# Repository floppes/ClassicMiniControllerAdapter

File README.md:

# Nintendo Classic Mini Controller USB Adapter #

This is an adapter for connecting one or two Nintendo Classic Mini controllers via USB to a computer.
It works with the controllers of a Nintendo NES and SNES Classic Mini.

## Motivation ##

I like playing old retro games on a Raspberry Pi running RetroPie on my TV screen. I also have a Nintendo SNES Classic Mini and like the quality and feel of its controllers. So why not connect the controllers to the Raspberry Pi? Well, Nintendo uses their own connectors and protocol which are incompatible with a PC/laptop/Raspberry Pi. But the connectors are available to buy on the Internet and the protocol specification can be found as well. So I created a small piece of hardware around an ATmega32U4 microcontroller to translate the controller's signals to USB.

## Hardware ##

This is basically an Arduino like the Leonardo or [SparkFun Pro Micro](https://www.sparkfun.com/products/12587), running two software I2C buses. It runs at 3.3 Volts and 8 MHz.

### LEDs ###

There are three LEDs on the board. The outer yellow LEDs indicate if a controller on the corresponding port was detected. The ports are hot-pluggable. The green LED in the center indicates that the device has booted and is operational.

### PCB ###

The PCB layout and part list can be found in [schematic](schematic).

You can order the unpopulated board directly from [OSH Park](https://oshpark.com/shared_projects/MKpWshOk).

Most parts can be bought from the usual distributors such as Farnell, DigiKey, Mouser etc. The connectors are a little bit harder to get. You can find them on eBay or AliExpress if you search for **Wiimote connector**. The components cost me about $11.

## Software ##

### Bootloader ###

I recommend flashing the SparkFun Pro Micro 3.3 V/8 MHz bootloader. Add the [SparkFun board definitions](https://github.com/sparkfun/Arduino_Boards) to your Arduino IDE. You will find the instructions on their GitHub page. Use the Arduino IDE together with an AVR programmer and the backside ICSP header of the board to burn the bootloader for the 3.3 V/8 MHz variant. If you don't have an AVR programmer, you can use an Arduino with the **ArduinoISP** sketch as a programmer.

Please note that the board operates at 3.3 V. Your programmer or Arduino must work with 3.3 V logic levels. Don't use 5 V levels! If your programmer supports 5 V and 3.3 V to power the board, set it to 3.3 V. I am using the [Diamex USB ISP programmer](https://www.diamex.de/dxshop/DIAMEX-USB-ISP-Programmer-Stick-fuer-AVR) which is inexpensive and works great.

### Firmware ###

The firmware (Arduino sketch) is located in [controller_adapter](controller_adapter) and uses the awesome [joystick library](https://github.com/MHeironimus/ArduinoJoystickLibrary) written by Matthew Heironimus. You will need to download and add it to your Arduino libraries before you can compile the firmware.

After burning the bootloader, the device should appear as a SparkFun Pro Micro when connected via USB to your computer. You can then compile and download the sketch with the Arduino IDE. Select the SparkFun Pro Micro 3.3 V/8 MHz device in the Arduino IDE.

### Windows ###

Windows will detect the board as two gamepads, no further drivers needed. Any modern game should be able to use the gamepads.

### Linux ###

Linux systems will detect only one controller by default. To make Linux detect both controllers, edit the file **/boot/cmdline.txt** and add

`usbhid.quirks=0x1b4f:0x9204:0x040`

## Case ##

I have created a case to protect the PCB. The case can be printed on a 3D printer. For the top part I recommend to print it with the front down to get the LED openings right. The top and bottom parts are held together be three M2 screws.

## License ##

The schematic, software and case are released under the Creative Commons BY-NC-SA 4.0 license. Check out [LICENSE.txt](LICENSE.txt) and the image link below for what you may and may not do with the files.

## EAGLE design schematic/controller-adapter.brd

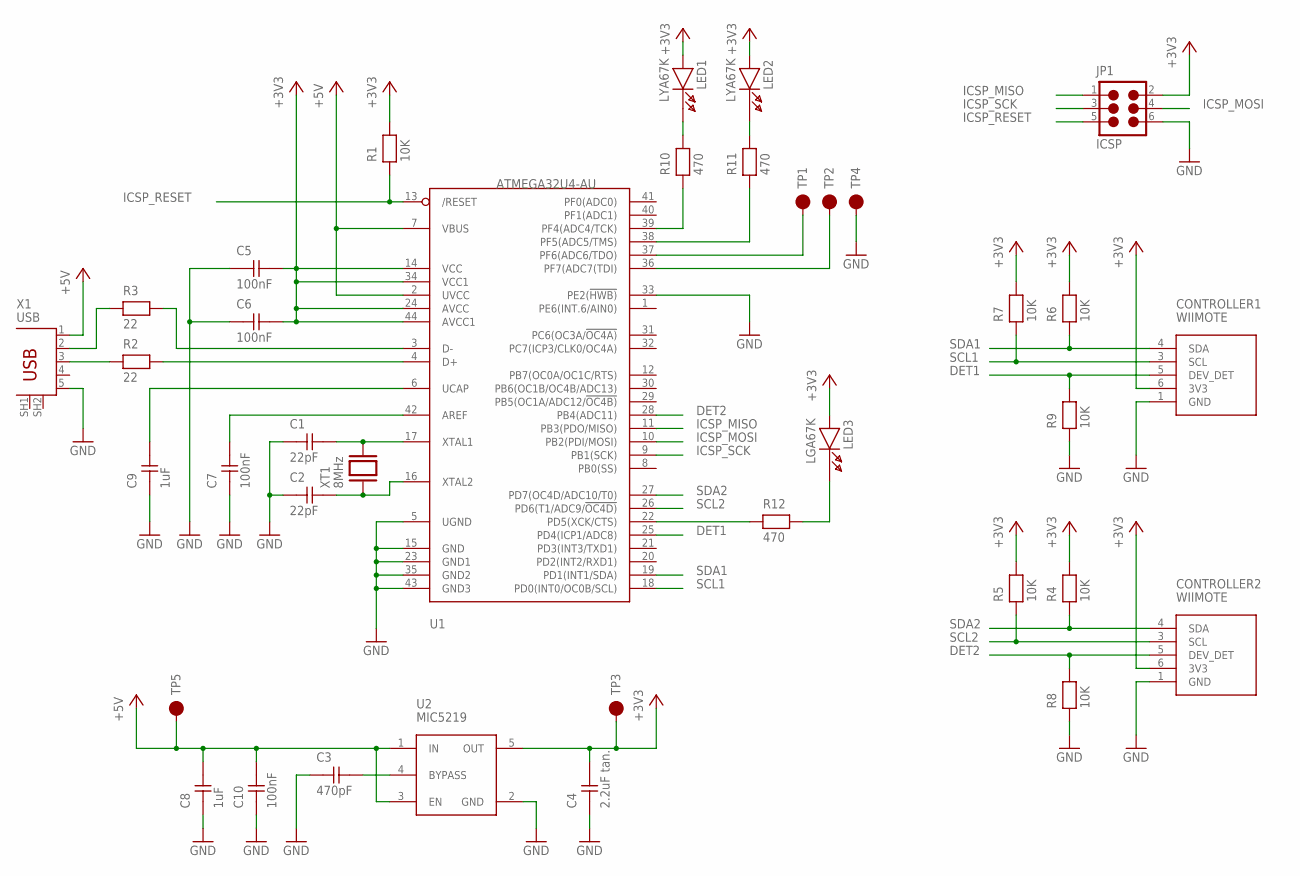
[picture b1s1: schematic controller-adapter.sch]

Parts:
C1, C2: 22pF; 0603
C3: 470pF; 0603
C4: 2.2uF tan.; 1206
C5, C6, C7, C10: 100nF; 0603
C8, C9: 1uF; 0603
CONTROLLER1, CONTROLLER2: WIIMOTE
JP1: ICSP; JP6
LED1, LED2: LYA67K; SIDELED
LED3: LGA67K; SIDELED
R1, R4, R5, R6, R7, R8, R9: 10K; 0603
R2, R3: 22; 0603
R10, R11, R12: 470; 0603
TP1: A1; TP1MM6
TP2: A0; TP1MM6
TP3: +3V3; TP1MM6
TP4: GND; TP1MM6
TP5: +5V; TP1MM6
U1: ATMEGA32U4-AU; TQFP44
U2: MIC5219; SOT23-5
X1: USB; USB_MICRO_B_PIN
XT1: 8MHz; ABM3B

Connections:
+3V3: C4.2, C5.2, C6.2, CONTROLLER1.6 (3V3), CONTROLLER2.6 (3V3), JP1.2, LED1.A, LED2.A, LED3.A, R1.2, R4.2, R5.2, R6.2, R7.2, TP3.1, U1.14 (VCC), U1.24 (AVCC), U1.34 (VCC1), U1.44 (AVCC1), U2.5 (OUT)
+5V: C8.2, C10.2, TP5.1, U1.2 (UVCC), U1.7 (VBUS), U2.1 (IN), U2.3 (EN), X1.1 (VBUS)
DET1: CONTROLLER1.5 (DEV_DET), R9.2, U1.25 (PD4(ICP1/ADC8))
DET2: CONTROLLER2.5 (DEV_DET), R8.2, U1.28 (PB4(ADC11))
GND: C1.1, C2.1, C3.1, C4.1, C5.1, C6.1, C7.1, C8.1, C9.1, C10.1, CONTROLLER1.1 (GND), CONTROLLER2.1 (GND), JP1.6, R8.1, R9.1, TP4.1, U1.5 (UGND), U1.15 (GND), U1.23 (GND1), U1.33 (PE2(!HWB)), U1.35 (GND2), U1.43 (GND3), U2.2 (GND), X1.5 (GND)
ICSP_MISO: JP1.1, U1.11 (PB3(PDO/MISO))
ICSP_MOSI: JP1.4, U1.10 (PB2(PDI/MOSI))
ICSP_RESET: JP1.5, R1.1, U1.13 (/RESET)
ICSP_SCK: JP1.3, U1.9 (PB1(SCK))
unnamed: C1.2, U1.17 (XTAL1), XT1.3 (2)
unnamed: C2.2, U1.16 (XTAL2), XT1.1
unnamed: TP1.1, U1.37 (PF6(ADC6/TDO))
unnamed: C3.2, U2.4 (BYPASS)
unnamed: R2.2, U1.4 (D+)
unnamed: R2.1, X1.3 (D+)
unnamed: R3.2, U1.3 (D-)
unnamed: R3.1, X1.2 (D-)
unnamed: TP2.1, U1.36 (PF7(ADC7(TDI))
unnamed: C7.2, U1.42 (AREF)
unnamed: C9.2, U1.6 (UCAP)
unnamed: R11.1, U1.38 (PF5(ADC5/TMS))
unnamed: R10.1, U1.39 (PF4(ADC4/TCK))
unnamed: LED1.K, R10.2
unnamed: LED2.K, R11.2
unnamed: R12.1, U1.22 (PD5(XCK/CTS))
unnamed: LED3.K, R12.2
SCL1: CONTROLLER1.3 (SCL), R7.1, U1.18 (PD0(INT0/OC0B/SCL))
SCL2: CONTROLLER2.3 (SCL), R5.1, U1.26 (PD6(T1/ADC9/!OC4D))
SDA1: CONTROLLER1.4 (SDA), R6.1, U1.19 (PD1(INT1/SDA))
SDA2: CONTROLLER2.4 (SDA), R4.1, U1.27 (PD7(OC4D/ADC10/T0))

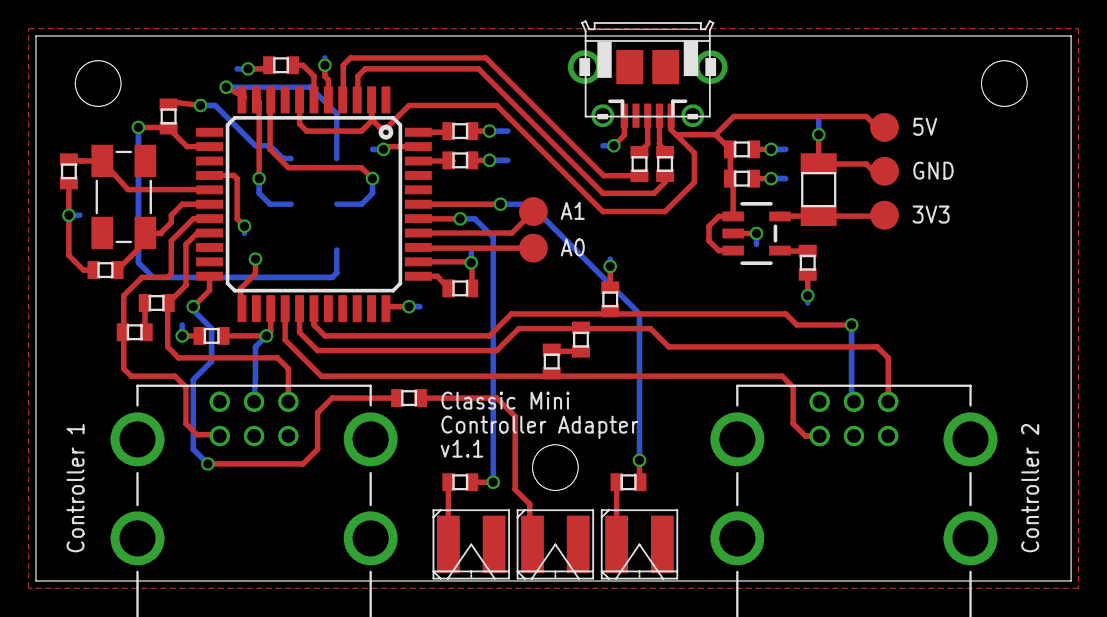
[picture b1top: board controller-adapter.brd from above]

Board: 2 copper layers, 57.5 x 30.3 mm, 37 parts (1 on the bottom side), 30 nets.

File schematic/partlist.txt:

Partlist

Exported from controller-adapter.sch at 16.05.2019 12:57:29

EAGLE Version 6.6.0 Copyright (c) 1988-2014 CadSoft

Assembly variant: 

Part        Value          Device            Package         Library            Sheet

C1          22pF           C0603             0603            controller-adapter 1
C2          22pF           C0603             0603            controller-adapter 1
C3          470pF          C0603             0603            controller-adapter 1
C4          2.2uF tan.     C1206             1206            controller-adapter 1
C5          100nF          C0603             0603            controller-adapter 1
C6          100nF          C0603             0603            controller-adapter 1
C7          100nF          C0603             0603            controller-adapter 1
C8          1uF            C0603             0603            controller-adapter 1
C9          1uF            C0603             0603            controller-adapter 1
C10         100nF          C0603             0603            controller-adapter 1
CONTROLLER1 WIIMOTE        WIIMOTE           WIIMOTE         controller-adapter 1
CONTROLLER2 WIIMOTE        WIIMOTE           WIIMOTE         controller-adapter 1
JP1         ICSP           JP6               JP6             controller-adapter 1
LED1        LYA67K         LEDSIDE           SIDELED         controller-adapter 1
LED2        LYA67K         LEDSIDE           SIDELED         controller-adapter 1
LED3        LGA67K         LEDSIDE           SIDELED         controller-adapter 1
R1          10K            R0603             0603            controller-adapter 1
R2          22             R0603             0603            controller-adapter 1
R3          22             R0603             0603            controller-adapter 1
R4          10K            R0603             0603            controller-adapter 1
R5          10K            R0603             0603            controller-adapter 1
R6          10K            R0603             0603            controller-adapter 1
R7          10K            R0603             0603            controller-adapter 1
R8          10K            R0603             0603            controller-adapter 1
R9          10K            R0603             0603            controller-adapter 1
R10         470            R0603             0603            controller-adapter 1
R11         470            R0603             0603            controller-adapter 1
R12         470            R0603             0603            controller-adapter 1
TP1         A1             TP1,6MM           TP1MM6          controller-adapter 1
TP2         A0             TP1,6MM           TP1MM6          controller-adapter 1
TP3         +3V3           TP1,6MM           TP1MM6          controller-adapter 1
TP4         GND            TP1,6MM           TP1MM6          controller-adapter 1
TP5         +5V            TP1,6MM           TP1MM6          controller-adapter 1
U1          ATMEGA32U4-AU  ATMEGA32U4-AU     TQFP44          controller-adapter 1
U2          MIC5219        MIC5219           SOT23-5         controller-adapter 1
X1          USB            USB_MICRO_B_MOLEX USB_MICRO_B_PIN controller-adapter 1
XT1         8MHz           XTABM3B           ABM3B           controller-adapter 1

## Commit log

2019-05-16 Source code moved from source to controller_adapter
2019-06-10 PDFs of schematic added
